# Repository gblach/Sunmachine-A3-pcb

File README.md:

# Sunmachine-A3-pcb
The driver for WS2812, SK6812 or similar LED strips controlled via Bluetooth LE.
It supports both RGB and WWA LEDs. This driver uses motion and light sensors, so in automatic mode
it can turn on the light when it detects someone's presence in the dark. The PCB is designed
for the [Hammond 1551V3](https://www.hammfg.com/electronics/small-case/plastic/1551v) enclosure,
so it can be hung on a wall or ceiling. The firmware for the board is available
in [Sunmachine-A3-fw](https://github.com/gblach/Sunmachine-A3-fw) repo and the mobile app
to control the board is available in [Sunmachine-app](https://github.com/gblach/Sunmachine-app)
repo.

## Key components
- [Raytac MDBT50-512K](https://www.raytac.com/product/ins.php?index_id=111) module with Nordic nRF52833 processor.
- RCWL-0516 microwave motion sensor.
- 5626 photodiode (5526 should work too).
- SN74LV1T34DBV level shifter.
- LM1117-3.3 voltage regulator.

## Connectors
- 2-pin ARK connector - for a power supply (5V).
- 3-pin ARK connector - for a LED strip (max. 6A).
- Tag-Connect 2050 - for a programmer.

## Production files
- [Gerber file](Sunmachine-A3.zip)
- [Bill of materials](Sunmachine-A3.csv)

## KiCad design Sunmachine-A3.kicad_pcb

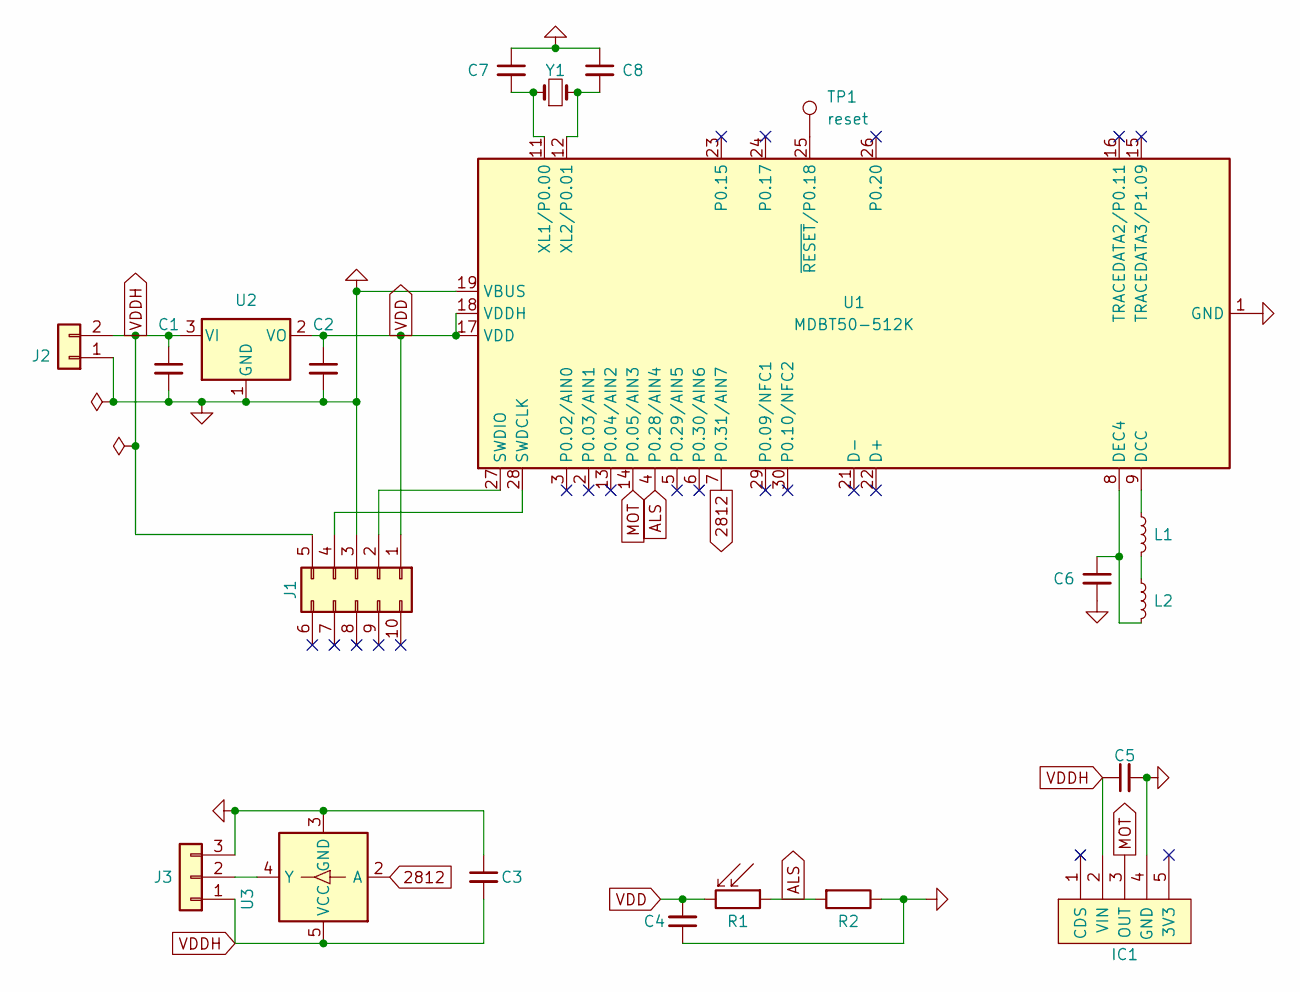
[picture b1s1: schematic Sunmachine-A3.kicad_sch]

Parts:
C1, C2, C3, C4, C5: 10uF; C_1206_3216Metric_Pad1.33x1.80mm_HandSolder; LCSC C15850
C6: 1uF; C_1206_3216Metric_Pad1.33x1.80mm_HandSolder
C7, C8: 12pF; C_1206_3216Metric_Pad1.33x1.80mm_HandSolder
IC1: RCWL-0516; RCWL-0516-3
J1: Conn_02x05_Counter_Clockwise; Tag-Connect_TC2050-IDC-NL_2x05_P1.27mm_Vertical_with_bottom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
J2: Conn_01x02; TerminalBlock_4Ucon_1x02_P3.50mm_Horizontal
J3: Conn_01x03; TerminalBlock_4Ucon_1x03_P3.50mm_Horizontal
L1: 10uH; L_1210_3225Metric_Pad1.42x2.65mm_HandSolder
L2: 15nH; L_1210_3225Metric_Pad1.42x2.65mm_HandSolder
R1: 5626; R_LDR_5.1x4.3mm_P3.4mm_Vertical
R2: 10k; R_1206_3216Metric_Pad1.30x1.75mm_HandSolder; LCSC C17902
TP1: reset; TestPoint_Pad_1.0x1.0mm
U1: MDBT50-512K; MDBT50
U2: LM1117-3.3; SOT-223-3_TabPin2; LCSC C6186
U3: SN74LV1T34DBV; SOT-23-5_HandSoldering; LCSC C100024
Y1: 32.768kHz, CL=9pF; Crystal_SMD_3215-2Pin_3.2x1.5mm

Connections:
2812: U1.7 (P0.31/AIN7), U3.2 (A)
ALS: R1.1, R2.2, U1.4 (P0.28/AIN4)
GND: C1.2, C2.2, C3.1, C4.1, C5.2, C6.2, C7.1, C8.1, IC1.4 (GND), J1.3, J2.1, J3.3, R2.1, U1.1 (GND), U1.10 (GND), U1.19 (VBUS), U1.20 (GND), U1.31 (GND), U2.1 (GND), U3.3 (GND)
MOT: IC1.3 (OUT), U1.14 (P0.05/AIN3)
unnamed: C6.1, L2.1, U1.8 (DEC4)
unnamed: C7.2, U1.11 (XL1/P0.00), Y1.1
unnamed: C8.2, U1.12 (XL2/P0.01), Y1.2
unnamed: J1.2, U1.27 (SWDIO)
unnamed: J1.4, U1.28 (SWDCLK)
unnamed: J3.2, U3.4 (Y)
unnamed: L1.1, L2.2
unnamed: L1.2, U1.9 (DCC)
unnamed 12: TP1.1, U1.25 (~RESET/P0.18); also elsewhere on the board
VDD: C2.1, C4.2, J1.1, R1.2, U1.17 (VDD), U1.18 (VDDH), U2.2 (VO)
VDDH: C1.1, C3.2, C5.1, IC1.2 (VIN), J1.5, J2.2, J3.1, U2.3 (VI), U3.5 (VCC)

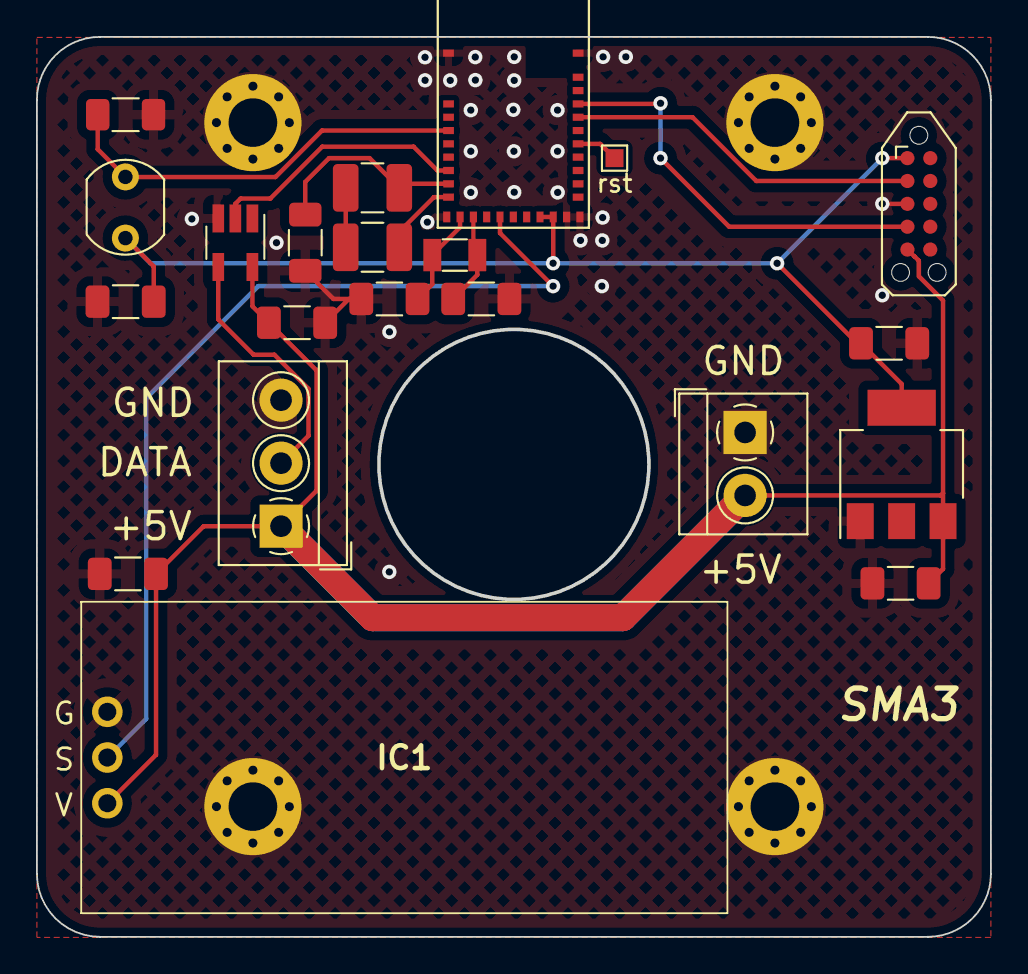
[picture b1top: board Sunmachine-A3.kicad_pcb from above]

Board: 2 copper layers, 52.9 x 49.9 mm, 21 parts (0 on the bottom side), 15 nets.

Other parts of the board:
rst: reset; TestPoint_Pad_1.0x1.0mm

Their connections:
unnamed 12: rst.1; also elsewhere on the board

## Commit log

2022-06-26 Initial import
